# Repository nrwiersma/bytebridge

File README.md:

<picture>
  <source media="(prefers-color-scheme: dark)" srcset="http://svg.wiersma.co.za/github/project.v2?title=bytebridge&tag=usb%20to%20uart&mode=dark">
  <source media="(prefers-color-scheme: light)" srcset="http://svg.wiersma.co.za/github/project.v2?title=bytebridge&tag=usb%20to%20uart">
  
</picture>

`ByteBridge` a USB to UART breakout board with more power.

Features:

* CP2102 bridge
* AMS1117 capable of delivering 1A

## Why

In 2025, dealing with Micro/Mini-USB is a pain. Additionally, most flash boards do not deliver
enough current to power a stock ESP32, making to process more difficult than it needs to be.

## Changelog

#### v0.1.0

* Initial schematic and board

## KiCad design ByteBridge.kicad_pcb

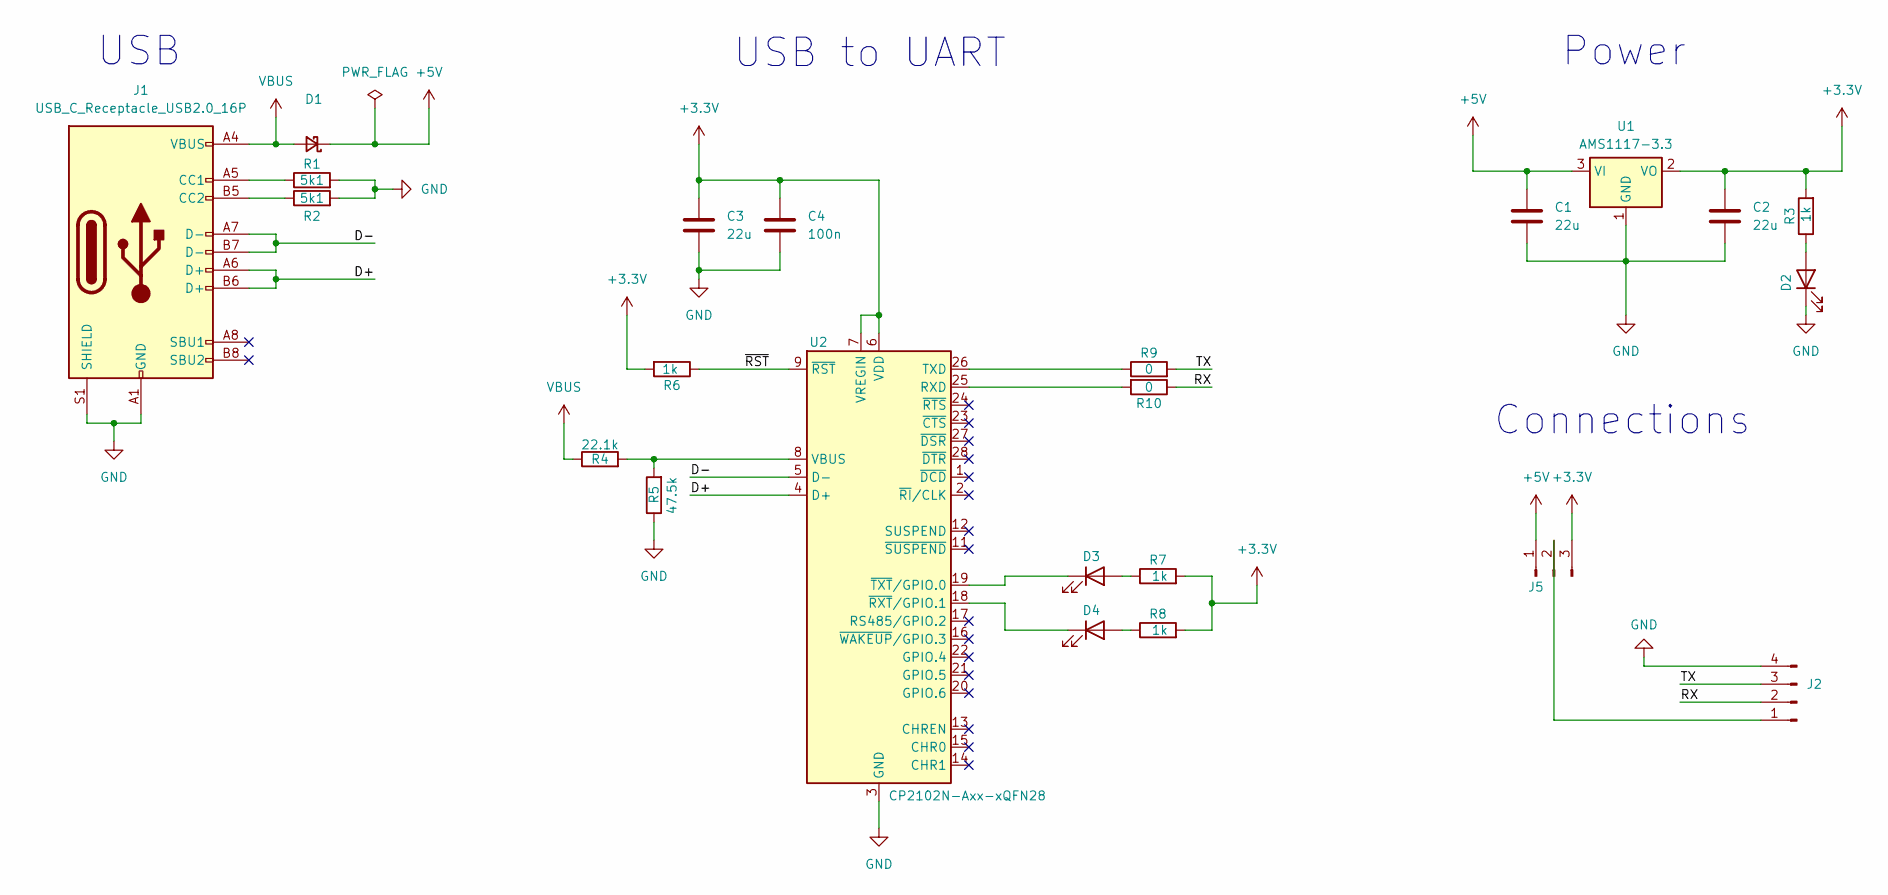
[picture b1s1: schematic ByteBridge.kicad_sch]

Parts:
C1, C2, C3: 22u; C_0603_1608Metric; MPN CL10A226MQ8NRNC; JLCPCB Part # C59461
C4: 100n; C_0603_1608Metric; MPN CL10B104KB8NNNC; JLCPCB Part # C1591
D1: D_Schottky_Small; D_SOD-323; MPN BAT760-7; JLCPCB Part # C124187
D2: LED; LED_0603_1608Metric; MPN LTST-C191KRKT; JLCPCB Part # C125099
D3, D4: LED; LED_0603_1608Metric; MPN LTST-C191GKT; JLCPCB Part # C99289
J1: USB_C_Receptacle_USB2.0_16P; USB_C_Receptacle_HRO_TYPE-C-31-M-12; MPN TYPE-C-31-M-12; JLCPCB Part # C165948
J2: Conn_01x04_Pin; PinHeader_1x04_P2.54mm_Vertical; MPN PZ254R-11-04P; JLCPCB Part # C492412
J5: Conn_01x03_Pin; PinHeader_1x03_P2.54mm_Vertical; MPN PZ254V-11-03P; JLCPCB Part # C2937625
R1, R2: 5k1; R_0402_1005Metric; MPN RC0402FR-075K1L; JLCPCB Part # C105872
R3, R6, R7, R8: 1k; R_0402_1005Metric; MPN RK73H1ETTP1001F; JLCPCB Part # C131360
R4: 22.1k; R_0402_1005Metric; MPN RC0402FR-0722K1L; JLCPCB Part # C163478
R5: 47.5k; R_0402_1005Metric; MPN RC0402FR-0747K5L; JLCPCB Part # C137974
R9, R10: 0; R_0402_1005Metric; MPN RC0402JR-070RL; JLCPCB Part # C60485
U1: AMS1117-3.3; SOT-223-3_TabPin2; MPN AMS1117-3.3; JLCPCB Part # C347222
U2: CP2102N-Axx-xQFN28; QFN-28-1EP_5x5mm_P0.5mm_EP3.35x3.35mm; MPN CP2102N-A02-GQFN28R; JLCPCB Part # C964632

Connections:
+3.3V: C2.1, C3.1, C4.1, J5.3, R3.2, R6.2, R7.2, R8.2, U1.2 (VO), U2.6 (VDD), U2.7 (VREGIN)
+5V: C1.1, D1.1 (K), J5.1, U1.3 (VI)
/D+: J1.A6 (D+), J1.B6 (D+), U2.4 (D+)
/D-: J1.A7 (D-), J1.B7 (D-), U2.5 (D-)
/RX: J2.2, R10.1
/TX: J2.3, R9.2
/~RST: R6.1, U2.9 (~RST)
GND: C1.2, C2.2, C3.2, C4.2, D2.1 (K), J1.A1 (GND), J1.A12 (GND), J1.B1 (GND), J1.B12 (GND), J1.S1 (SHIELD), J2.4, R1.2, R2.2, R5.1, U1.1 (GND), U2.3 (GND), U2.29 (GND)
unnamed: D2.2 (A), R3.1
unnamed: D3.2 (A), R7.1
unnamed: D3.1 (K), U2.19 (~TXT/GPIO.0)
unnamed: D4.2 (A), R8.1
unnamed: D4.1 (K), U2.18 (~RXT/GPIO.1)
unnamed: J1.A5 (CC1), R1.1
unnamed: J1.B5 (CC2), R2.1
unnamed: J2.1, J5.2
unnamed: R10.2, U2.25 (RXD)
unnamed: R9.1, U2.26 (TXD)
unnamed: R4.2, R5.2, U2.8 (VBUS)
VBUS: D1.2 (A), J1.A4 (VBUS), J1.A9 (VBUS), J1.B4 (VBUS), J1.B9 (VBUS), R4.1

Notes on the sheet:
Connections
USB
Power
USB to UART

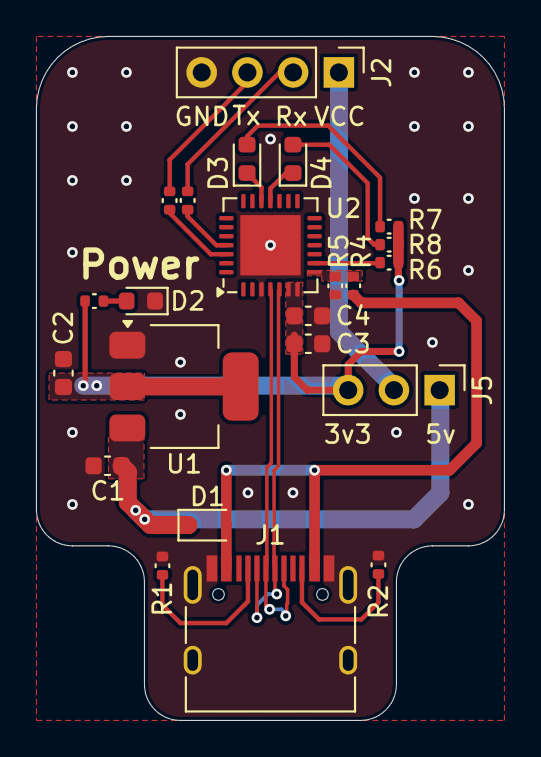
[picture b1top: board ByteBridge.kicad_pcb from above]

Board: 2 copper layers, 26.0 x 38.0 mm, 23 parts (0 on the bottom side), 20 nets.

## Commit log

2025-05-26 chore: initial commit
2025-05-27 feat: initial board
2025-06-03 feat: refactor board edge and component placement
2025-06-04 fix: spelling
2025-06-04 feat: initial board (#1)
2026-01-04 chore: add reader header
2026-01-04 chore: update board image

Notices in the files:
README.md:
License: MIT
